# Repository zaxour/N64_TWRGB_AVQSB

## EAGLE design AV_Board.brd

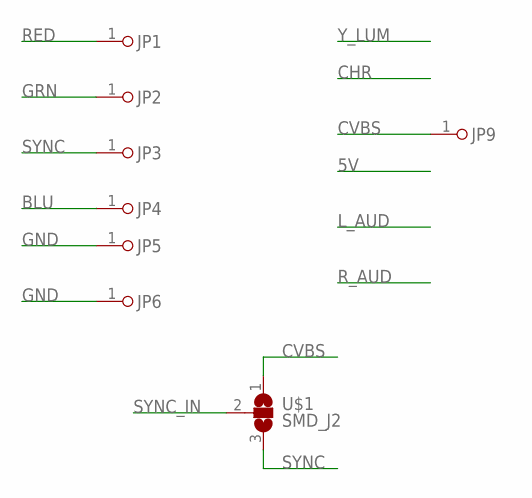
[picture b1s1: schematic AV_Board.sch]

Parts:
JP1, JP2, JP3, JP4, JP5, JP6, JP9: PINHD-1X1; 1X01
U$1: SMD_J2; SJ_2

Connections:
BLU: JP4.1
CVBS: JP9.1, U$1.1
GND: JP5.1, JP6.1
GRN: JP2.1
RED: JP1.1
SYNC: JP3.1, U$1.3
SYNC_IN: U$1.2

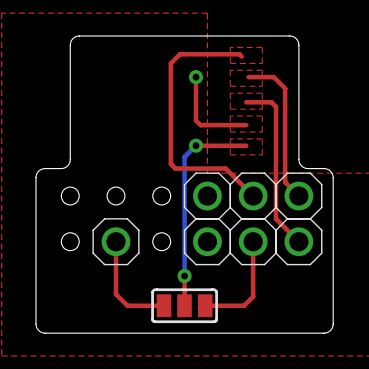
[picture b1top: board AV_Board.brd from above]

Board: 2 copper layers, 16.5 x 16.5 mm, 8 parts (0 on the bottom side), 3 nets.
